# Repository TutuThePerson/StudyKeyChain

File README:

A small-portable study companion that motivates you to study!!! (probably). Its purpose is to play voice clips (initially in my own voice lol, but you could ask your teacher's voice - Mr Tuton watchout :) ), it aims to run fixed focus session and reminds you to take a break and hyrdrate all in the formfactor of a keychain.

Why did I build this?

No clue.jk. I just finished 2 months of A-levels and being grinding those past papers for atleast half a year now; I realise it is really demoralising to be studying 3 in the morning alone - so this idea stemmed from those experiences. It's just a bit of fun really and isn't aimed as a full replacement for regular discipline and proper revision but might provide that little push to keep studying while staying healthy. I didn't want a big, bulky solution so I thought it would be cool if I could fit it on a keychain, that I could hang on my bag as such.
The StudyPal consists of a 2 layer PCB, larger than a regular keycap but still small enough to put in your pocket or hang on your bag. It runs an ESP32-S3, with audio functiionality (physically hidden under the keycap)

Functions:

1. It goes throgh focus sessions on variable length via the rotary encoder under the keycap.
2. It has audio playback through a speaker which aims to play motivational audio clips, session start-end cues and hydration reminders.
3. OLED display which shows timer, session stats and break progress througha slim slanted window on the keycap.
4. Keycap - short press for motivational cue, long press to end a session early or to power off
5. Hidden Rotary Encoder undeer the keycap to adjust session length
6. Battery powered via a single-cell LiPo with USB C charging and ESD protection

Schematic:

The keychain is designed to be small,rechargable and portable. Acting as a study companion of sorts. It has a keycap which can be pressed as well as
a small screen to display a timer and messages. Has a speaker to announce messages and volume nob to adjust the sound level.

Components:
Display: 
https://thepihut.com/products/0-96-oled-display-module-128x64?variant=42810024820931&country=GB&currency=GBP&utm_medium=product_sync&utm_source=google&utm_content=sag_organic&utm_campaign=sag_organic&gad_source=1&gad_campaignid=11673057096&gbraid=0AAAAADfQ4GFnqqNToS8p5asC_NSDni8WB&gclid=Cj0KCQjwornRBhCrARIsAON5exGcvCFGRJbs2rZYKfWSv5leMXklEiwZfUrHGDKcCYuu_vIVaE8o2x4aAtSMEALw_wcB
0.96 Inch OLED Display Module 128x64
Microcontroller: ESP32-S3-WROOM-1-N8
 - Needs on board storage, lower power consumption
Audio amplifier:max98357a
Speaker: 28mm 8 ohm 1watt 
https://shop.pimoroni.com/products/mini-oval-speaker-8-ohm-1-watt?variant=31150555267155
Buzzer: Piezo
Mechanical Switch: Kalih Choc V1
Rotary encoder: EC11 encoder switch with push button
Battery:803040 LiPoi 3.7V 1000mAh
Charging IC: TP4056 
USB C connector: 16 pin USB C connector
Status LED: just a led really
LDO: AP2112K-3.3 a
Power Switch: TPL5111 Soft latch 

SCHEMATIC EXPLANATION:

Blocks:
- Audio Amplifier: Amplifies the audio signal from the microcontroller to drive the speaker.
- LDO Voltage Regulator: Provides stable 3.3V output to other components
- OLED Display: Responsible for displaying the timer and motivational messages.
- Rotary Encoder: Allows user to adjust volume
- Testpoints: To test and debug the circuit (during development)
- PWR Flag: Tells Kicad that the net is intentially powered
- Battery voltage sensor: Monitors the battery voltage
- Battery connector: Connects the battery to the PCB
- Piezoelectric buzzer: Used to generate sound for alerts and notifications.
- Speaker: Outputs audio messages and alerts
- Flash/Reset Buttons: Used to reset the microcontroller or flash new firmware
- Charging Circuit: Manages the charging of the battery through the USB C connector
- Power Timer: Manages power state of the device 
- Microcontroller Unit: Processing Unit of the device, manages firmware and provides native USB for flashing and debugging
- USB Connector + Protection: Provides USB connectivity and protection for the microcontroller

- Audio Amplifier:
 - VDD PIN is connected directly to 3.3V and in parallel to 2 decoupling capacitors (10uF and 0.1uF) to reduce noise with the power rail.
 - The 100k resistor connected to "SD_MODE" pulls up the voltage and sets the chip to stereo mode. 
 - I^2S signals connect directly the microcontroller

- LDO Voltage Regulator:
 - Takes battery voltage and regulates it down to 3.3V for the microcontroller and other components.
 - 10uF capacitor stabilises the output voltage and reduces noise.
 - EN pin is tied to VBAT_SW meaning that no seperate enable control is needed as LDO is enabled whenever MOSFET delivers power

- OLED Display:
 - I^2C signals connect directly to the microcontroller
 - 4.7k pullup resistors set the I^2C bus to a hgih state
 - Powered by 3.3V rail

- Rotary Encoder:
 - Rotary Encoder with integrated push switch, A,B and C are rotary signals and SW is the push button signal.
 - 10k pullup resistors are used on A, B and SW maintains correct logic states when not being actuated, 100nf Caps supress contact noise
 - C is connected to ground so pressing the switch pulls signal lines to a LOW state

- Testpoints:
 - Just testing points really. No special usecase (just used for testing)

- PWR flag:
 - just a kicad symbol that tells electric rules that net has an intentional power source. No special usecase

- Battery voltage sensor:
 - Potential divider with two 100k resistors halving the battery voltage so fits ESP32 input range
 - Firmware intends to read the reported voltage and multiplies by 2 to get the actual battery voltage
 - (High resistance values chosen to reduce current draw, extending battery life)

- Battery connector:
 - Standard JST-PH 2 pin connector which matches most hobby LiPo batteries. 

- Piezoelectric buzzer:
 - Directly driven by GPIO11 (ESP32 IO11 pin)
 - Used for short audible click noises

- Speaker:
 - 8 Ohmn Speaker, low power draw.
 - just a speaker really.

- Flash/Reset Buttons:
 - Safety net during development in case something goes wrong. ESP supports autoamtic flash entry over native USB

- Charging Circuit:
 - TP4056 charger handles charging of the LiPo battery through the USB C connector.
 - 1.2k resistor sets the charging current to 1A, which is safe for the 1000mAh battery.
 - Red LED indicates charging, green LED indicates fully charged.

- Power Timer:
 - Soft Latch timer keeps device on after a buttojn press release and turns it off when firware signals completion from the "DONE" pin
 - "DELAY" pin connected to +BATT to set manual mode
 - Mosfet allows circuit to fully disconnect LDO from battery power for zero-current standby

- Microcontroller Unit:
 - 8MB flash varaint, used to hold firmware and voice clips etc
 - Has native USB for flashing and debugging
 - Strapping pins (GPIO0, GPIO45, GPIO46) tied to logic states set by pullup/down resistors.

- USB Connector + Protection:
 - USB 2.0 (not super fast)
 - D+ and D- lines shorted so it works both ways
 - Protection chip protects MCU from electrostatic discharge
 - 5.1k pulldown resistors (as required by USB C spec)

Assembly:
 - Make sure you have all components listed available and casing 3D printed.
 - Solder all the components on the PCB as per the schematic
 - Connect the battery to the 2 pin connector (label in schematic file)
 - Place the PCB on top of the base and use M3 screws, preferably around 3-4mm
 - Flash firmware onto the ESP32 using the USB-C connector (If there is no output when flashing, hold the flash button to reset - forces chip into download mode)
 - Use plastic adhesive to adhere the the lid to the base - once everything works okay
 - Put on the keycap and enjoy!

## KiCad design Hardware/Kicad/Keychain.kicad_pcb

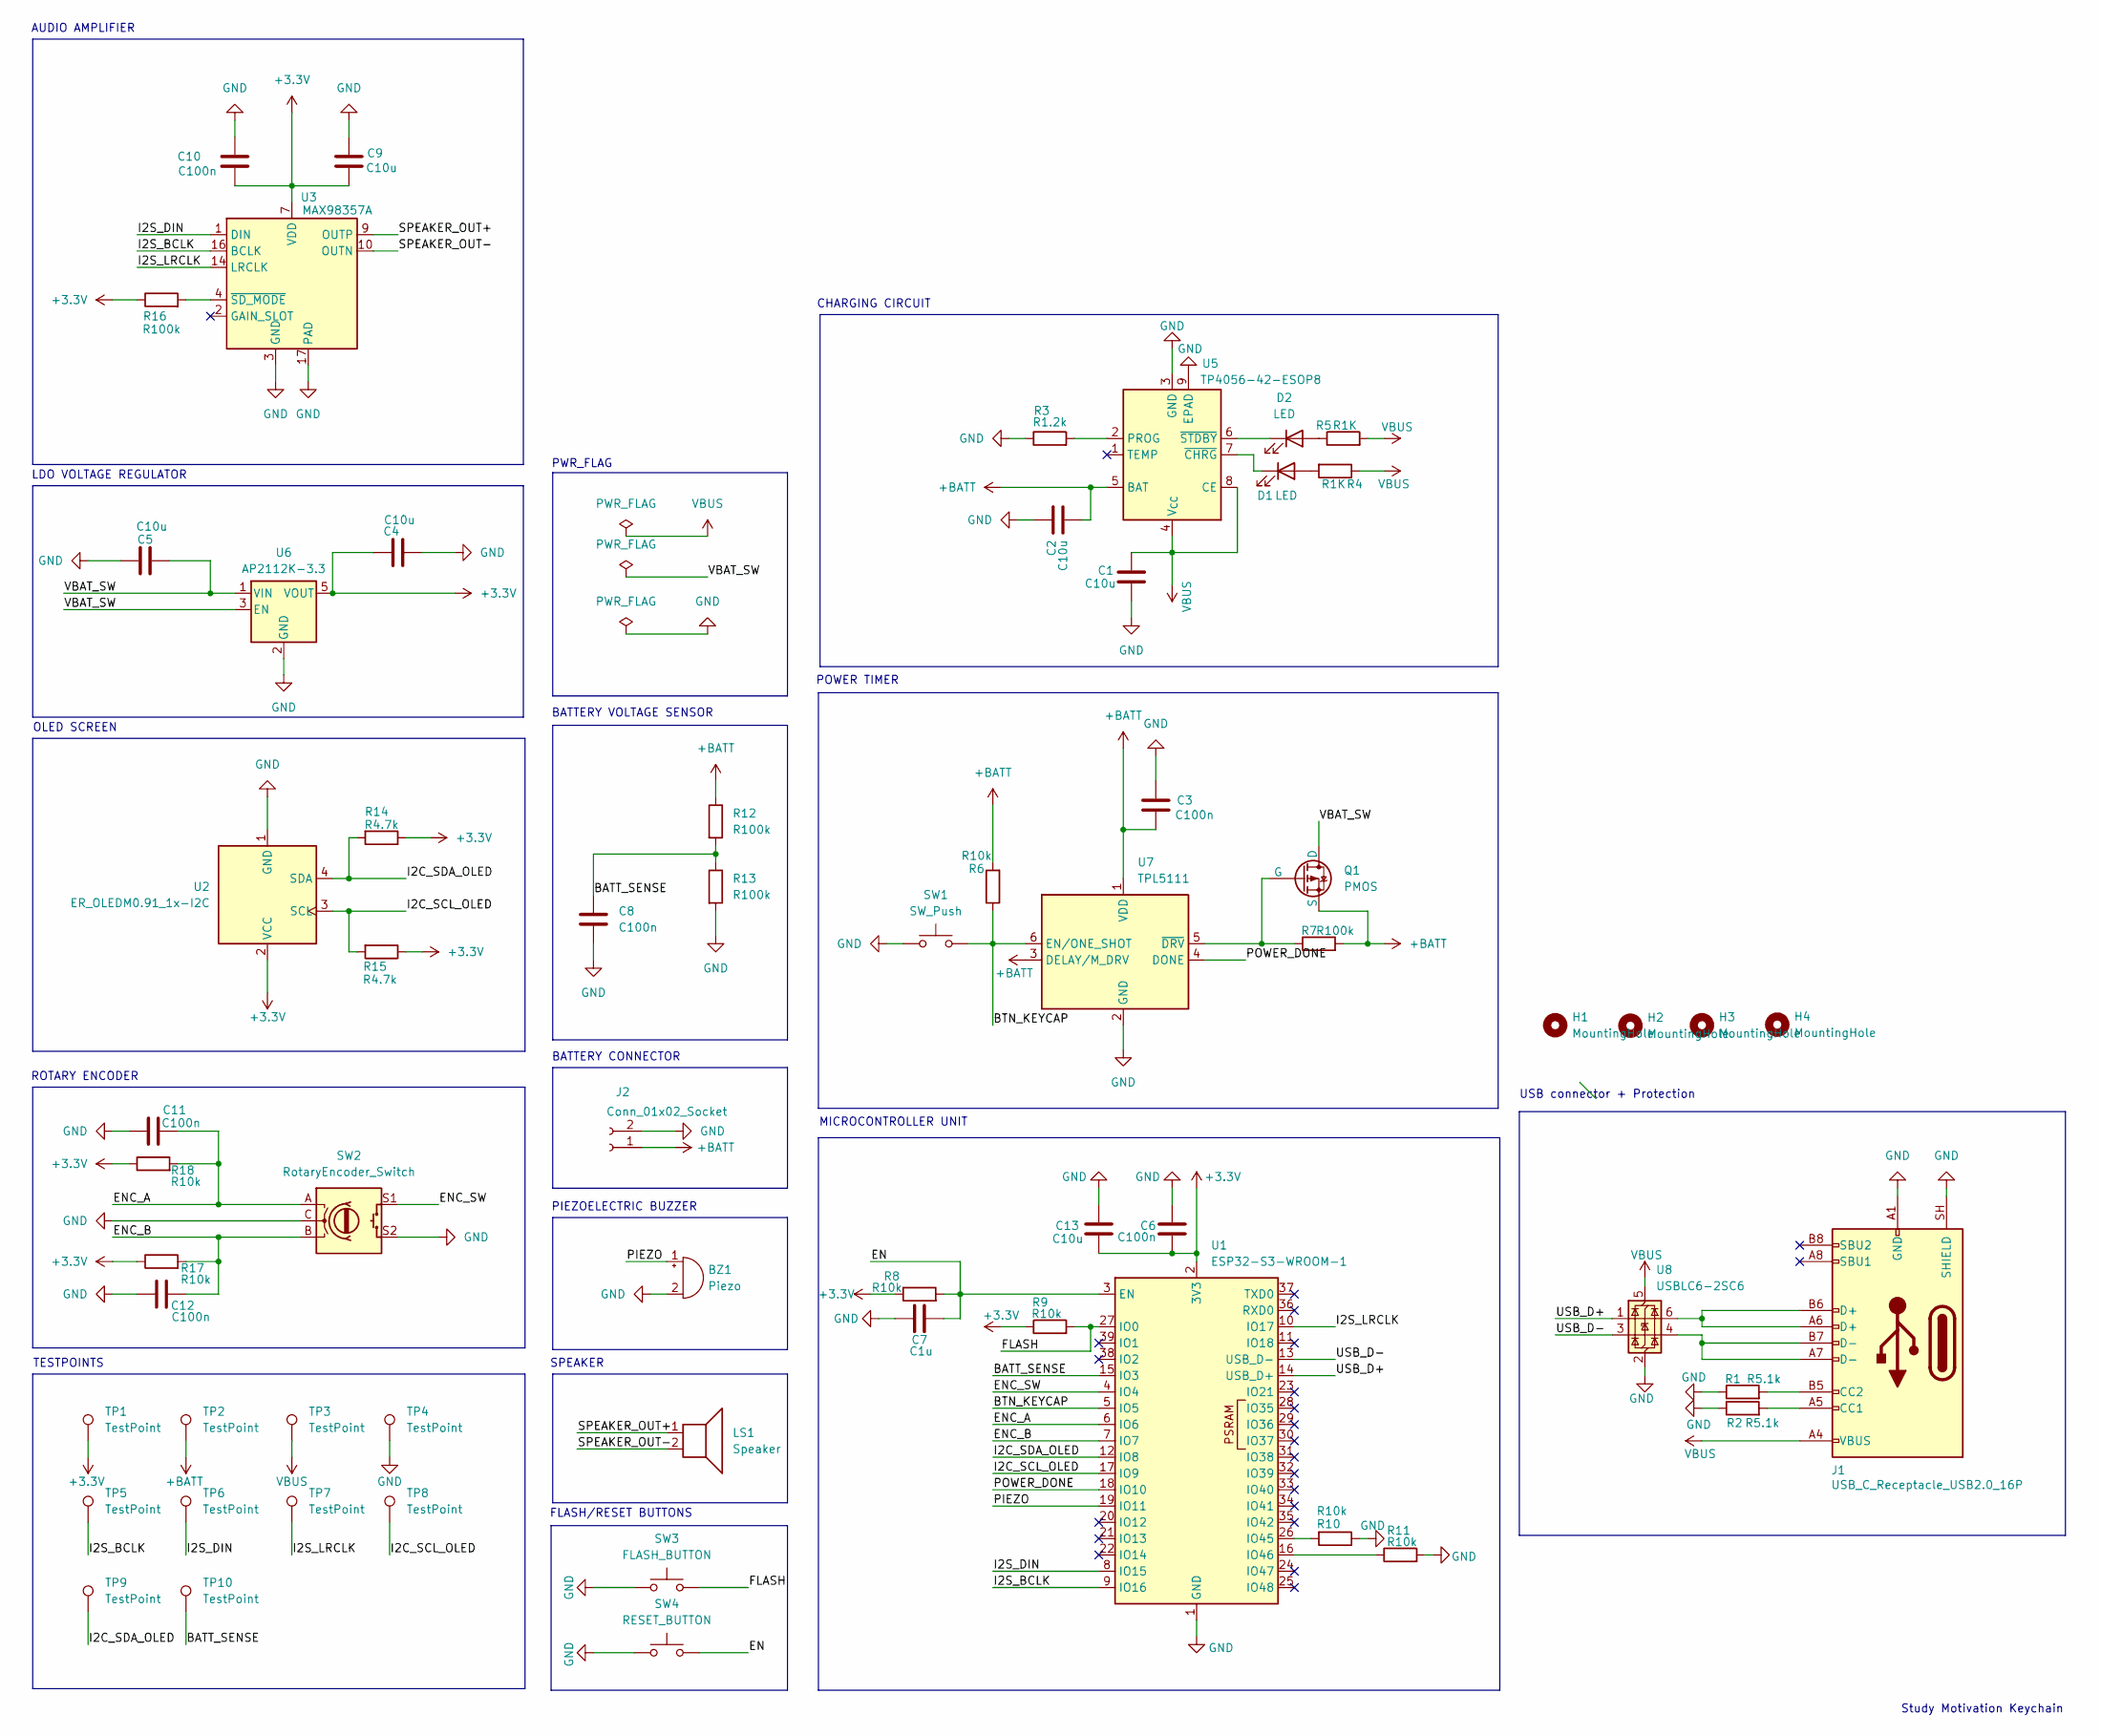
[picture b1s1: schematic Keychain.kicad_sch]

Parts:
BZ1: Piezo; Buzzer_12x9.5RM7.6
C1, C2, C4, C5, C9, C13: C10u; C_0402_1005Metric
C3, C6, C8, C10, C11, C12: C100n; C_0402_1005Metric
C7: C1u; C_0402_1005Metric
D1, D2: LED; LED_0603_1608Metric
H1, H2, H3, H4: MountingHole; MountingHole_3.2mm_M3
J1: USB_C_Receptacle_USB2.0_16P; USB_C_Receptacle_Amphenol_124019772112A
J2: Conn_01x02_Socket; JST_PH_S2B-PH-K_1x02_P2.00mm_Horizontal
LS1: Speaker; PinSocket_1x02_P2.00mm_Vertical
Q1: PMOS; SOT-23-5
R1, R2: R5.1k; R_0402_1005Metric
R3: R1.2k; R_0402_1005Metric
R4, R5: R1K; R_0402_1005Metric
R6, R8, R9, R10, R11, R17, R18: R10k; R_0402_1005Metric
R7, R12, R13, R16: R100k; R_0402_1005Metric
R14, R15: R4.7k; R_0402_1005Metric
SW1: SW_Push; SW_Kailh_Choc_V1_1.00u
SW2: RotaryEncoder_Switch; RotaryEncoder_Alps_EC11E-Switch_Vertical_H20mm
SW3: FLASH_BUTTON; SW_PUSH_6mm
SW4: RESET_BUTTON; SW_PUSH_6mm
TP1, TP2, TP3, TP4, TP5, TP6, TP7, TP8, TP9, TP10: TestPoint; TestPoint_Pad_2.0x2.0mm
U1: ESP32-S3-WROOM-1
U2: ER_OLEDM0.91_1x-I2C
U3: MAX98357A; TQFN-16-1EP_3x3mm_P0.5mm_EP1.23x1.23mm
U5: TP4056-42-ESOP8; SOIC-8-1EP_3.9x4.9mm_P1.27mm_EP2.41x3.3mm_ThermalVias
U6: AP2112K-3.3; SOT-23-5
U7: TPL5111; SOT-23-6
U8: USBLC6-2SC6; SOT-23-6

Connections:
+3.3V: C4.1, C6.1, C9.2, C10.2, C13.1, R8.1, R9.1, R14.1, R15.1, R16.1, R17.1, R18.1, TP1.1 (1_1), U1.2 (3V3), U2.2 (VCC), U3.7 (VDD), U3.8 (VDD), U6.5 (VOUT)
+BATT: C2.1, C3.1, J2.1, Q1.3 (S), R6.2, R7.2, R12.1, TP2.1 (1_1), U5.5 (BAT), U7.1 (VDD), U7.3 (DELAY/M_DRV)
/<NO NET>: TP7.1 (1_1), U1.10 (IO17), U3.14 (LRCLK)
/BATT_SENSE: C8.1, R12.2, R13.1, TP10.1 (1_1), U1.15 (IO3)
/BTN_KEYCAP: R6.1, SW1.2, U1.5 (IO5), U7.6 (EN/ONE_SHOT)
/EN: C7.2, R8.2, SW4.2, U1.3 (EN)
/ENC_A: C11.2, R18.2, SW2.A, U1.6 (IO6)
/ENC_B: C12.2, R17.2, SW2.B, U1.7 (IO7)
/ENC_SW: SW2.S1, U1.4 (IO4)
/FLASH: R9.2, SW3.2, U1.27 (IO0)
/I2C_SCL_OLED: R15.2, TP8.1 (1_1), U1.17 (IO9), U2.3 (SCL)
/I2C_SDA_OLED: R14.2, TP9.1 (1_1), U1.12 (IO8), U2.4 (SDA)
/I2S_BCLK: TP5.1 (1_1), U1.9 (IO16), U3.16 (BCLK)
/I2S_DIN: TP6.1 (1_1), U1.8 (IO15), U3.1 (DIN)
/PIEZO: BZ1.1 (+), U1.19 (IO11)
/POWER_DONE: U1.18 (IO10), U7.4 (DONE)
/SPEAKER_OUT+: LS1.1, U3.9 (OUTP)
/SPEAKER_OUT-: LS1.2, U3.10 (OUTN)
/USB_D+: U1.14 (USB_D+), U8.1 (I/O1)
/USB_D-: U1.13 (USB_D-), U8.3 (I/O2)
/VBAT_SW: C5.1, Q1.1 (D), U6.1 (VIN), U6.3 (EN)
GND: BZ1.2 (-), C1.2, C2.2, C3.2, C4.2, C5.2, C6.2, C7.1, C8.2, C9.1, C10.1, C11.1, C12.1, C13.2, J1.A1 (GND), J1.A12 (GND), J1.B1 (GND), J1.B12 (GND), J1.SH (SHIELD), J2.2, R1.1, R2.1, R3.1, R10.1, R11.2, R13.2, SW1.1, SW2.C, SW2.S2, SW3.1, SW4.1, TP4.1 (1_1), U1.1 (GND), U1.40 (GND), U1.41 (GND), U2.1 (GND), U3.3 (GND), U3.11 (GND), U3.15 (GND), U3.17 (PAD), U5.3 (GND), U5.9 (EPAD), U6.2 (GND), U7.2 (GND), U8.2 (GND)
unnamed: D1.2 (A), R4.2
unnamed: D1.1 (K), U5.7 (~CHRG)
unnamed: D2.2 (A), R5.1
unnamed: D2.1 (K), U5.6 (~STDBY)
unnamed: J1.A5 (CC1), R2.2
unnamed: J1.B5 (CC2), R1.2
unnamed: J1.A6 (D+), J1.B6 (D+), U8.6 (I/O1)
unnamed: J1.A7 (D-), J1.B7 (D-), U8.4 (I/O2)
unnamed: Q1.2 (G), R7.1, U7.5 (~DRV)
unnamed: R10.2, U1.26 (IO45)
unnamed: R11.1, U1.16 (IO46)
unnamed: R16.2, U3.4 (~SD_MODE)
unnamed: R3.2, U5.2 (PROG)
VBUS: C1.1, J1.A4 (VBUS), J1.A9 (VBUS), J1.B4 (VBUS), J1.B9 (VBUS), R4.1, R5.2, TP3.1 (1_1), U5.4 (V_{CC}), U5.8 (CE), U8.5 (VBUS)

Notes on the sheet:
LDO VOLTAGE REGULATOR
TESTPOINTS
ROTARY ENCODER
POWER TIMER
MICROCONTROLLER UNIT
PIEZOELECTRIC BUZZER
BATTERY CONNECTOR
SPEAKER
FLASH/RESET BUTTONS
Study Motivation Keychain
PWR_FLAG
AUDIO AMPLIFIER
BATTERY VOLTAGE SENSOR
OLED SCREEN
CHARGING CIRCUIT
USB connector + Protection

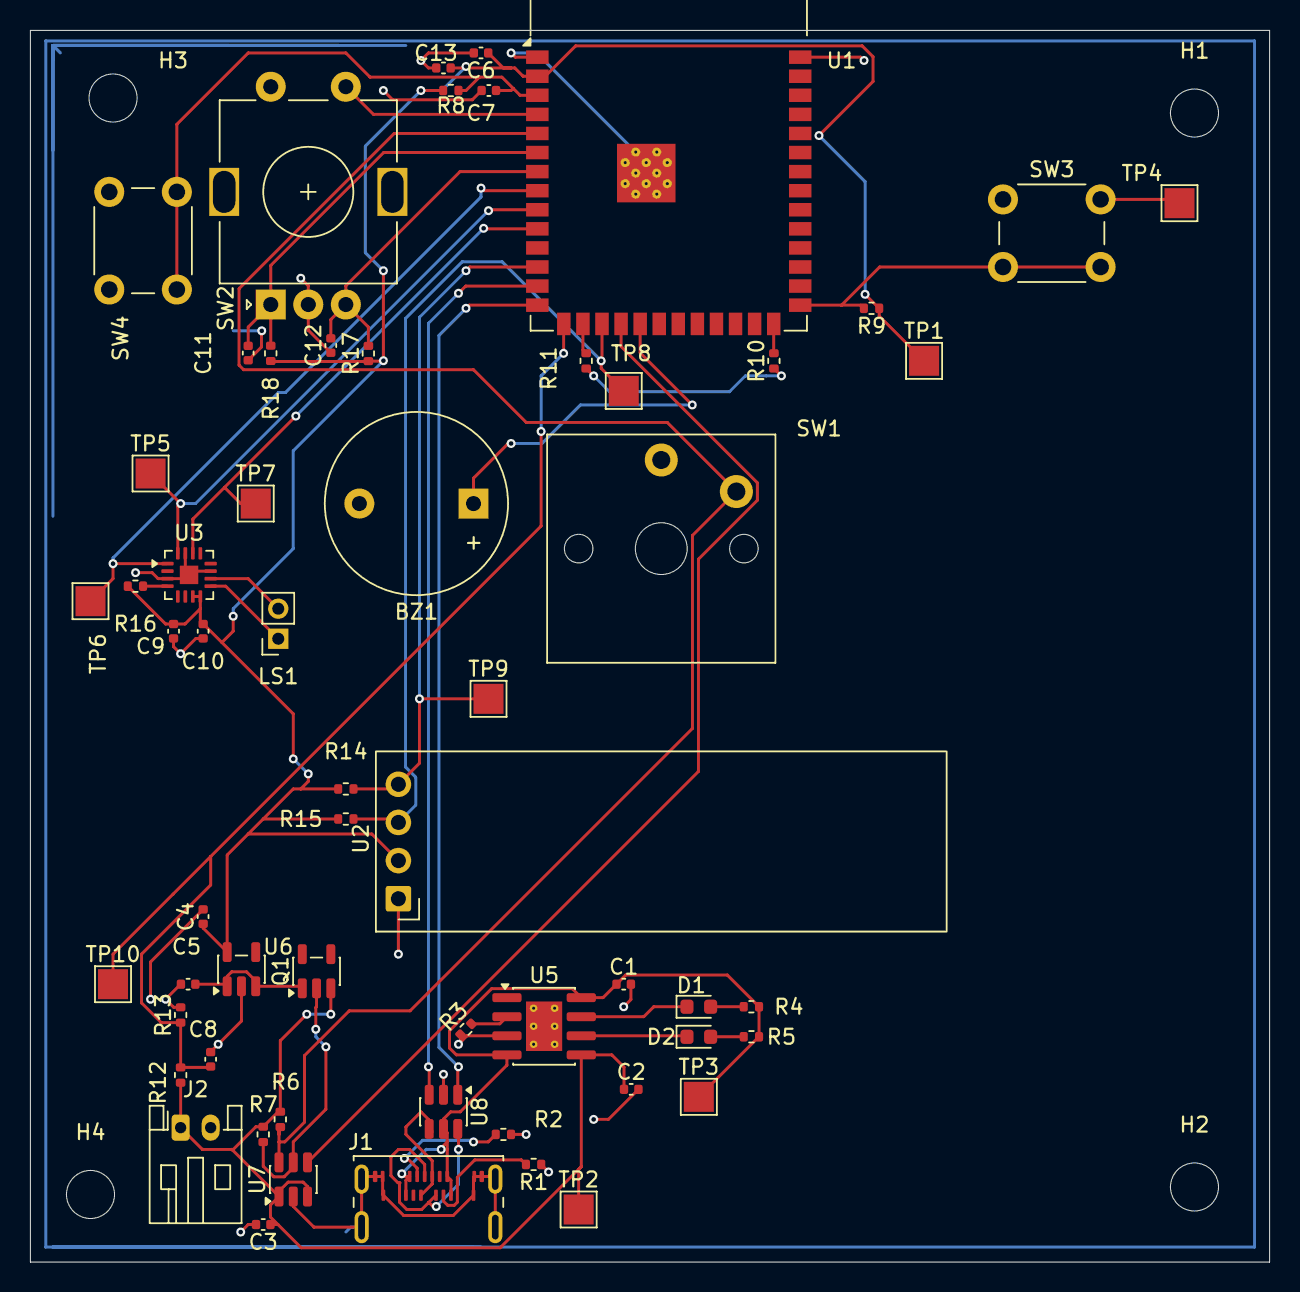
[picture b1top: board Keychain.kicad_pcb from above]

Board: 2 copper layers, 82.5 x 82.0 mm, 63 parts (0 on the bottom side), 36 nets.

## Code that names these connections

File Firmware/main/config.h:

#pragma once

//#############
// This file contains the pin assignments for the study keychain project
//#############

// Button (Kalih Choc Switch)
#define PIN_BUTTON 5

// Rotary encoder
#define PIN_ENCODER_A 6
#define PIN_ENCODER_B 7
#define PIN_ENCODER_SW 4 

//I^2C (Oled Display)
#define PIN_i2C_SDA 12
#define PIN_i2C_SCL 17
#define I2C_FREQ_HZ 400000
#define OLED_ADDRESS 0x3C

// I^2S (audio amplifier)
#define PIN_I2S_DIN 8
#define PIN_I2S_BCLK 9
#define PIN_I2S_LRCLK 10

// Piezoelectric (audio feedback)
#define PIN_PIEZO 11

// Power Management 
#define PIN_POWER_DONE 18
#define PIN_BATTERY_SENS 15

//#############
//constants
//#############

//Study Session Duration (fixed)

#define SESSION_DEFAULT_SECONDS 3300
#define BREAK_DURATION_SECONDS 300

//Reminder

#define HYDRATION_REMINDER_SECONDS 3300

// Battery Monitoring
#define POTENTIAL_DIVIDER_RATIO 2.0f 
#define FULL_BATT_mV 4200
#define BATT_EMPTY_mV 3000
#define BATT_LOW_mV 3300

// Audio 
#define I2S_SAMPLE_RATE 16000 
#define I2S_BUFFER_SIZE 1024

// other UI/timing
#define IDLE_TIMEOUT_mS 30000
#define POWER_OFF_TIMEOUT_mS 14400000
#define LONG_PRESS_mS 2000
#define DEBOUNCE_mS 30

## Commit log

2026-06-15 Added Schematic, and updated README
2026-06-16 Create Zine.png
    Added zine
2026-06-16 update readme - instructions
2026-06-19 Written code, built some of it.
2026-06-19 Update code - not checked
2026-06-19 checked code
2026-06-19 Enhance README with project details and features
    Expanded the README to provide detailed information about the StudyPal project, including its purpose, functions, components, and design.
2026-06-19 Add README.md file
2026-06-19 Enhance README with technical details and assembly guide
    Added detailed technical specifications and assembly instructions for the keychain project, including components, power subsystem, audio setup, and PCB design.
2026-06-19 Fix typos and enhance clarity in README.md
    Corrected minor typographical errors and improved clarity in the README.
2026-06-19 Add BOM table to README
    Added a table for the Bill of Materials (BOM) section in the README.
2026-06-19 Update BOM in README with component details
    Added detailed BOM with item names, quantities, prices, and URLs for components.
2026-06-19 Bug Crushed and built
2026-06-19 Update README with assembly and design notes
    Added assembly instructions and design notes to README.
2026-06-19 Add MIT License to the project
2026-06-19 Formatting
2026-06-19 Update Zine image link from PDF to PNG
2026-06-19 Updated zine
2026-06-19 Convert BOM file to CSV format
    Updated the BOM format from tab-separated to CSV format.
2026-06-19 Add .gitignore file with common patterns
2026-06-19 Revise README for improved clarity and organization
    Updated README.md to enhance clarity and structure, including sections on functions, technical details, and assembly instructions.
2026-06-19 Fix typos in README.md
    Corrected typos in the README file for clarity.
